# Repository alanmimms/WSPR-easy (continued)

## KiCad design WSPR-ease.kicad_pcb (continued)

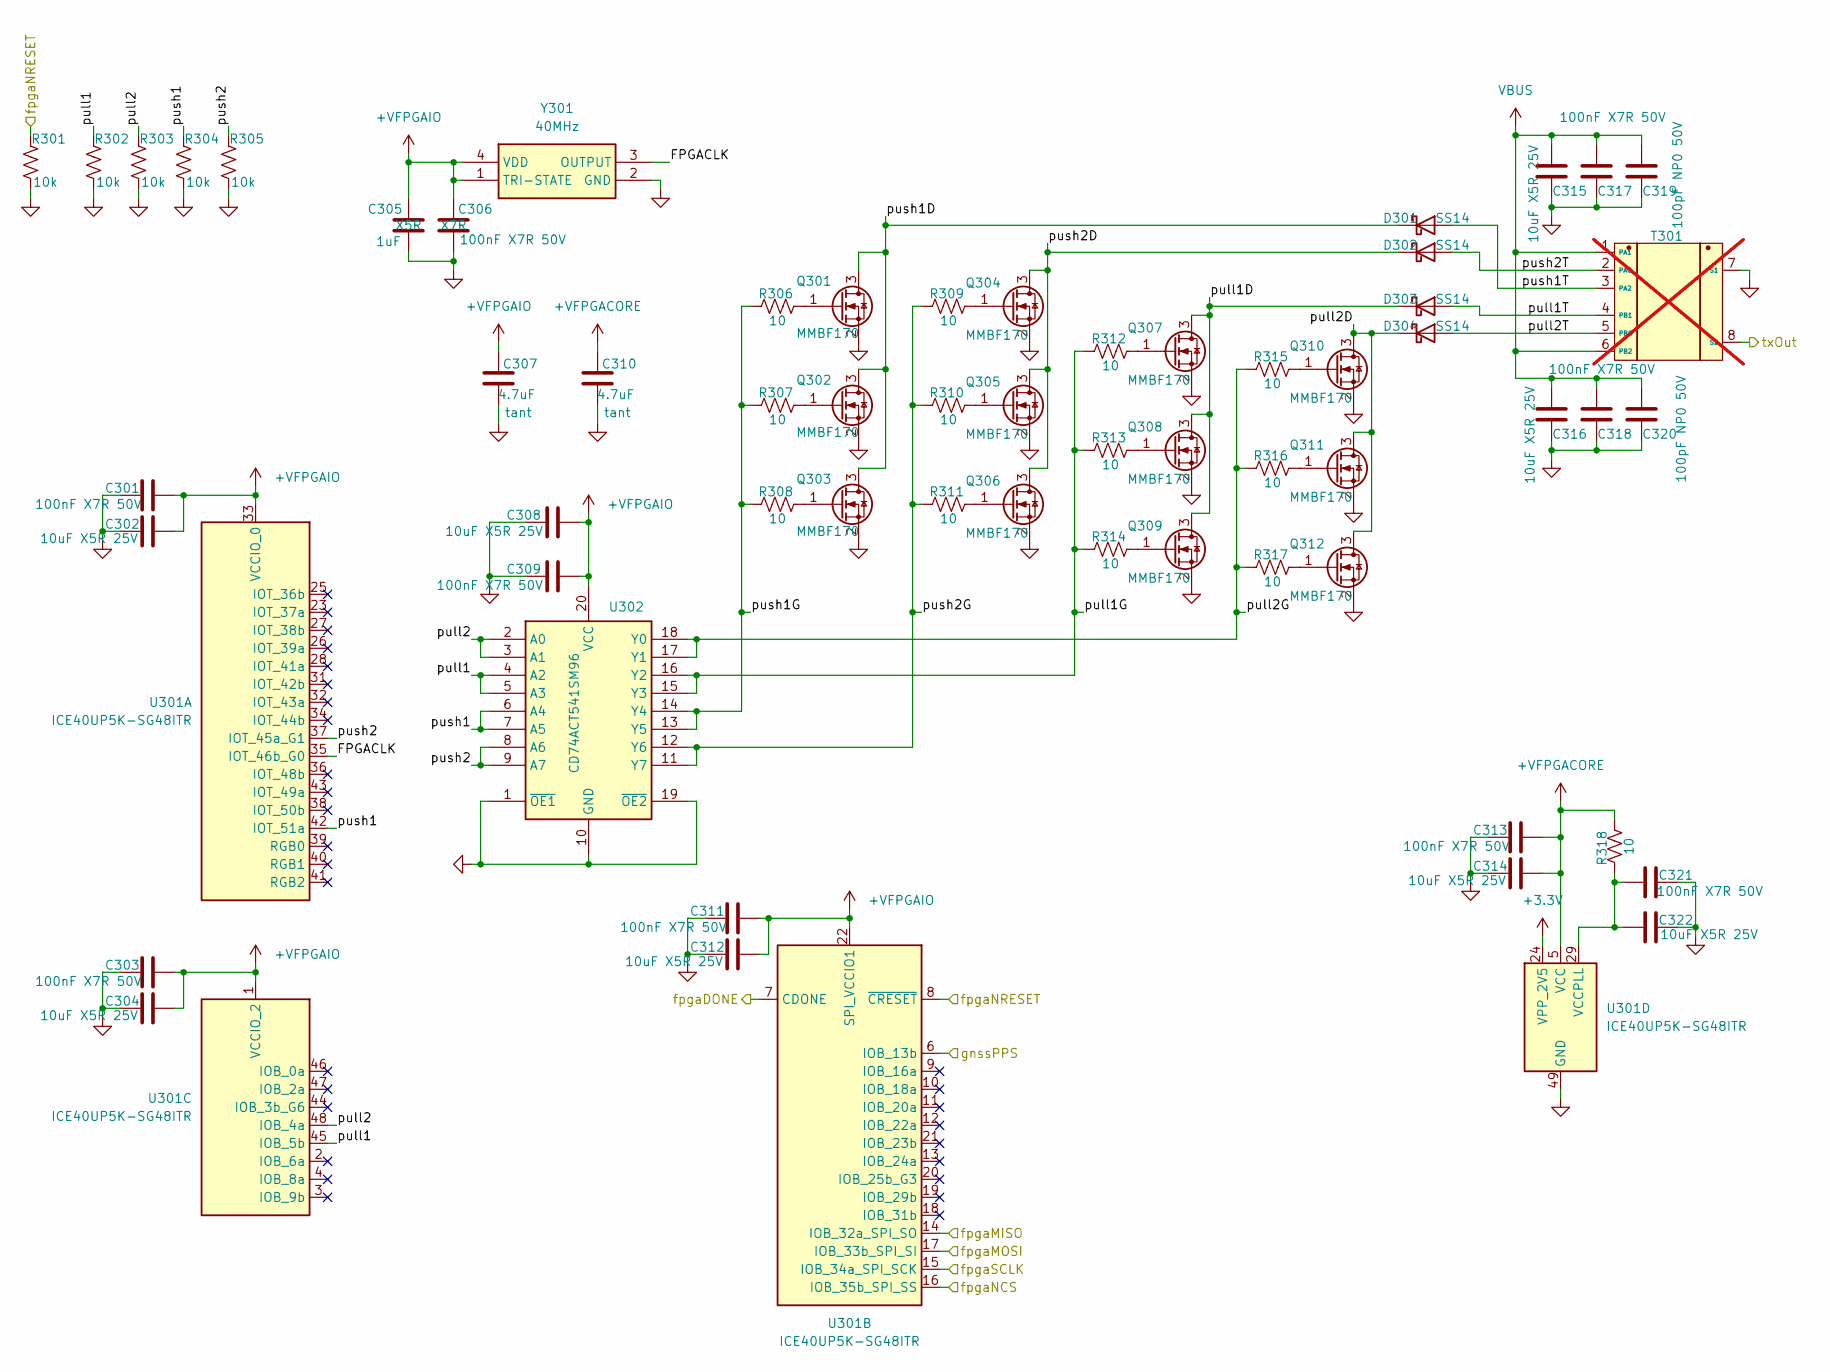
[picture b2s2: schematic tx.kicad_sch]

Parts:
C301, C303, C309, C311, C313, C317, C318, C321: 100nF X7R 50V; C_0603_1608Metric; LCSC C24452
C302, C304, C308, C312, C314, C315, C316, C322: 10uF X5R 25V; C_0603_1608Metric; LCSC C96446
C305: 1uF; C_0402_1005Metric; Mouser_PN 81-GRM155R61E105KE1D; LCSC_PN C301928
C306: 100nF X7R 50V; C_0603_1608Metric; Mouser_PN 80-C0805F104K1RAUTO; LCSC_PN C24452
C307, C310: 4.7uF; C_0402_1005Metric; Mouser_PN 74-298D475X9010M2T; LCSC_PN C18535241
C319, C320: 100pF NP0 50V; C_0402_1005Metric; LCSC C106200
D301, D302, D303, D304: SS14; D_SMA; LCSC C83852
Q301, Q302, Q303, Q304, Q305, Q306, Q307, Q308, Q309, Q310, Q311, Q312: MMBF170; SOT-23; LCSC C28871
R301, R302, R303, R304, R305: 10k; R_0402_1005Metric; LCSC C60490
R306, R307, R308, R309, R310, R311, R312, R313, R314, R315, R316, R317, R318: 10; R_0603_1608Metric; LCSC C2907091
T301: BN-43-202_DualPri_CTSec; bn-43-202-horizontal; MPN 2843000202; LCSC C7174817; not fitted
U301: ICE40UP5K-SG48ITR; QFN-48-1EP_7x7mm_P0.5mm_EP5.6x5.6mm; LCSC C2678152
U302: CD74ACT541SM96; SOP65P780X200-20N; LCSC C553178
Y301: 40MHz; ECSTXO201633400TR; MPN ECS-TXO-2016-33-400-TR; LCSC_PN C2451471

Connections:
+3.3V: U301.24 (VPP_2V5); also elsewhere on the board
+VFPGACORE: C310.1, C313.2, C314.2, R318.2, U301.5 (VCC), U301.30 (VCC); also elsewhere on the board
+VFPGAIO: C301.2, C302.2, C303.2, C304.2, C305.1, C306.1, C307.1, C308.2, C309.2, C311.2, C312.2, U301.1 (VCCIO_2), U301.22 (SPI_VCCIO1), U301.33 (VCCIO_0), U302.20 (VCC), Y301.1 (TRI-STATE), Y301.4 (VDD); also elsewhere on the board
/Low Pass Filters/RFin: T301.8 (S2); also elsewhere on the board
/Transmitter/FPGACLK: U301.35 (IOT_46b_G0), Y301.3 (OUTPUT)
/Transmitter/pull1: R302.1, U301.45 (IOB_5b), U302.4 (A2), U302.5 (A3)
/Transmitter/pull1D: D303.1 (K), Q307.3 (D), Q308.3 (D), Q309.3 (D)
/Transmitter/pull1G: R312.1, R313.1, R314.1, U302.15 (Y3), U302.16 (Y2)
/Transmitter/pull1T: D303.2 (A), T301.4 (PB1)
/Transmitter/pull2: R303.1, U301.48 (IOB_4a), U302.2 (A0), U302.3 (A1)
/Transmitter/pull2D: D304.1 (K), Q310.3 (D), Q311.3 (D), Q312.3 (D)
/Transmitter/pull2G: R315.1, R316.1, R317.1, U302.17 (Y1), U302.18 (Y0)
/Transmitter/pull2T: D304.2 (A), T301.5 (PBC)
/Transmitter/push1: R304.1, U301.42 (IOT_51a), U302.6 (A4), U302.7 (A5)
/Transmitter/push1D: D301.1 (K), Q301.3 (D), Q302.3 (D), Q303.3 (D)
/Transmitter/push1G: R306.1, R307.1, R308.1, U302.13 (Y5), U302.14 (Y4)
/Transmitter/push1T: D301.2 (A), T301.3 (PA2)
/Transmitter/push2: R305.1, U301.37 (IOT_45a_G1), U302.8 (A6), U302.9 (A7)
/Transmitter/push2D: D302.1 (K), Q304.3 (D), Q305.3 (D), Q306.3 (D)
/Transmitter/push2G: R309.1, R310.1, R311.1, U302.11 (Y7), U302.12 (Y6)
/Transmitter/push2T: D302.2 (A), T301.2 (PAC)
/fpgaDONE: U301.7 (CDONE); also elsewhere on the board
/fpgaMISO: U301.14 (IOB_32a_SPI_SO); also elsewhere on the board
/fpgaMOSI: U301.17 (IOB_33b_SPI_SI); also elsewhere on the board
/fpgaNCS: U301.16 (IOB_35b_SPI_SS); also elsewhere on the board
/fpgaNRESET: R301.1, U301.8 (~CRESET); also elsewhere on the board
/fpgaSCLK: U301.15 (IOB_34a_SPI_SCK); also elsewhere on the board
/gnssPPS: U301.6 (IOB_13b); also elsewhere on the board
GND: C301.1, C302.1, C303.1, C304.1, C305.2, C306.2, C307.2, C308.1, C309.1, C310.2, C311.1, C312.1, C313.1, C314.1, C315.1, C316.1, C317.1, C318.1, C319.1, C320.1, C321.1, C322.1, Q301.2 (S), Q302.2 (S), Q303.2 (S), Q304.2 (S), Q305.2 (S), Q306.2 (S), Q307.2 (S), Q308.2 (S), Q309.2 (S), Q310.2 (S), Q311.2 (S), Q312.2 (S), R301.2, R302.2, R303.2, R304.2, R305.2, T301.7 (S1), U301.49 (GND), U302.1 (~OE1), U302.10 (GND), U302.19 (~OE2), Y301.2 (GND); also elsewhere on the board
unnamed: Q301.1 (G), R306.2
unnamed: Q302.1 (G), R307.2
unnamed: Q303.1 (G), R308.2
unnamed: Q304.1 (G), R309.2
unnamed: Q305.1 (G), R310.2
unnamed: Q306.1 (G), R311.2
unnamed: Q307.1 (G), R312.2
unnamed: Q308.1 (G), R313.2
unnamed: Q309.1 (G), R314.2
unnamed: Q310.1 (G), R315.2
unnamed: Q311.1 (G), R316.2
unnamed: Q312.1 (G), R317.2
unnamed: C321.2, C322.2, R318.1, U301.29 (VCCPLL)
VBUS: C315.2, C316.2, C317.2, C318.2, C319.2, C320.2, T301.1 (PA1), T301.6 (PB2); also elsewhere on the board

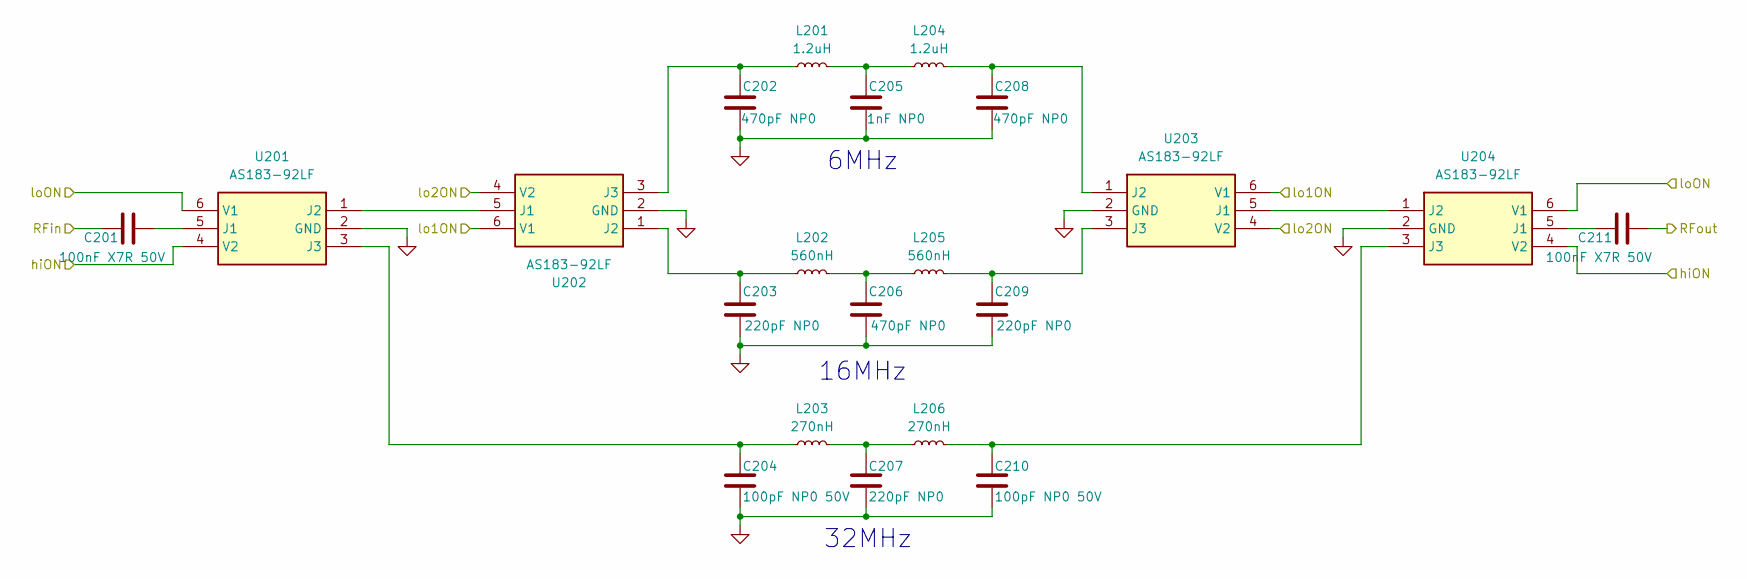
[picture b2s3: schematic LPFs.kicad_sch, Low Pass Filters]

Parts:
C201, C211: 100nF X7R 50V; C_0603_1608Metric; LCSC C24452
C202, C206, C208: 470pF NP0; C_0402_1005Metric; LCSC C106259
C203, C207, C209: 220pF NP0; C_0402_1005Metric; LCSC C107001
C204, C210: 100pF NP0 50V; C_0402_1005Metric; LCSC C106200
C205: 1nF NP0; C_0402_1005Metric; LCSC C5182455
L201, L204: 1.2uH; L_1008_2520Metric; Mouser Part Number 1008LS-222; LCSC C2044063
L202, L205: 560nH; L_0805_2012Metric; Mouser Part Number 0805CS-391XGLC; LCSC C6364717
L203, L206: 270nH; L_0805_2012Metric; Mouser Part Number 0805CS-271 XGLC; LCSC C404430
U201, U202, U203, U204: AS183-92LF; SOT65P220X110-6N; Mouser Part Number 873-AS183-92LF

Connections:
/Low Pass Filters/RFin: C201.1; also elsewhere on the board
/Low Pass Filters/RFout: C211.2; also elsewhere on the board
/hiON: U201.4 (V2), U204.4 (V2); also elsewhere on the board
/lo1ON: U202.6 (V1), U203.6 (V1); also elsewhere on the board
/lo2ON: U202.4 (V2), U203.4 (V2); also elsewhere on the board
/loON: U201.6 (V1), U204.6 (V1); also elsewhere on the board
GND: C202.2, C203.2, C204.2, C205.2, C206.2, C207.2, C208.2, C209.2, C210.2, U201.2 (GND), U202.2 (GND), U203.2 (GND), U204.2 (GND); also elsewhere on the board
unnamed: C205.1, L201.2, L204.1
unnamed: C206.1, L202.2, L205.1
unnamed: C207.1, L203.2, L206.1
unnamed: C201.2, U201.5 (J1)
unnamed: U201.1 (J2), U202.5 (J1)
unnamed: C204.1, L203.1, U201.3 (J3)
unnamed: C203.1, L202.1, U202.1 (J2)
unnamed: C202.1, L201.1, U202.3 (J3)
unnamed: U203.5 (J1), U204.1 (J2)
unnamed: C208.1, L204.2, U203.1 (J2)
unnamed: C209.1, L205.2, U203.3 (J3)
unnamed: C211.1, U204.5 (J1)
unnamed: C210.1, L206.2, U204.3 (J3)

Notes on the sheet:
6MHz
32MHz
16MHz

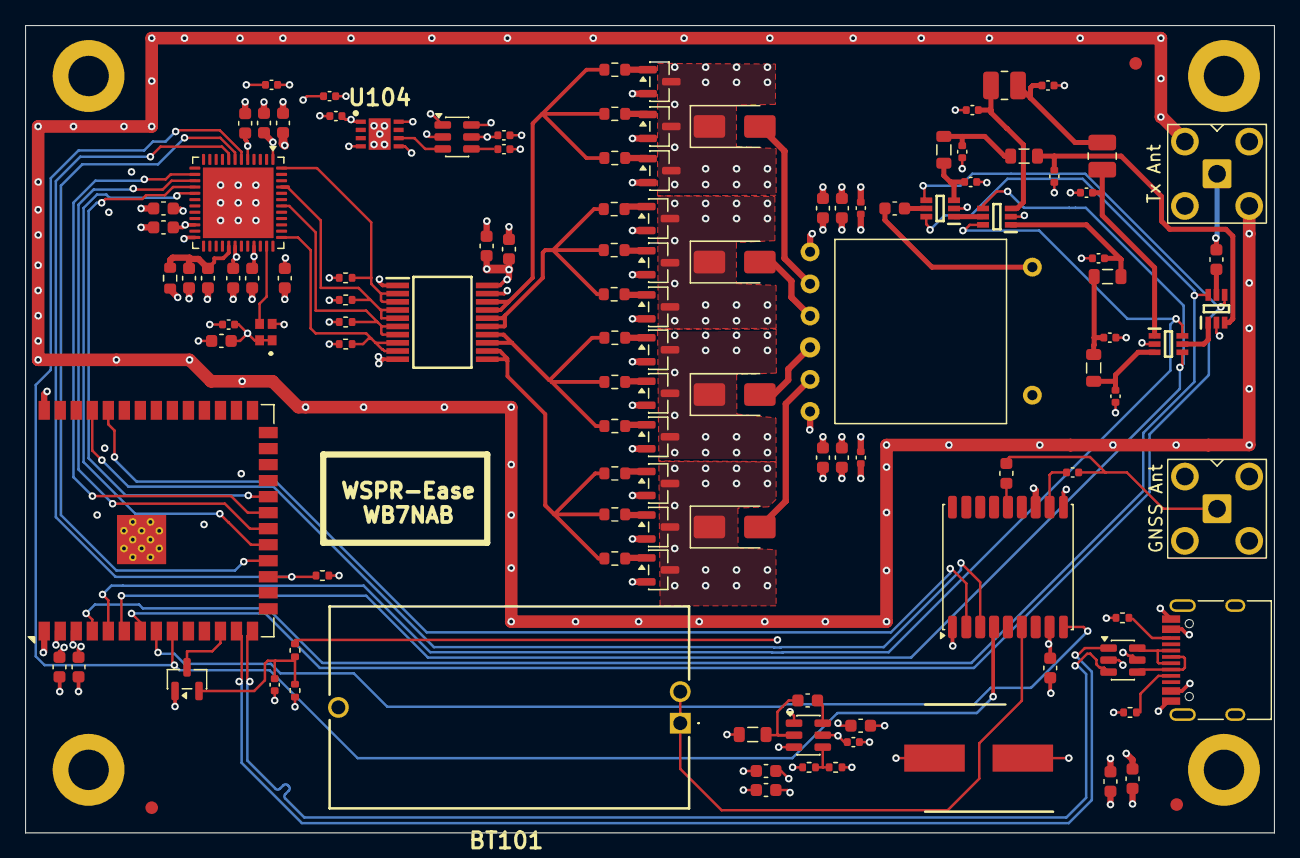
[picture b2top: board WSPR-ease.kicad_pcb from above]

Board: 4 copper layers, 99.0 x 64.0 mm, 123 parts (0 on the bottom side), 81 nets.

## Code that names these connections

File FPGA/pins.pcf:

# Clock Inputs
set_io fpgaSCLK_pin 15
set_io clk40 35
set_io gnssPPS 6

# SPI Interface (Standard 4mA is fine for these)
set_io fpgaMOSI 17
set_io fpgaNCS 16
set_io fpgaMISO 14

# RF Exciter Outputs (DDR Capable, 12mA High Drive)
set_io rfPushBase 42
set_io rfPushPeak 37
set_io rfPullBase 45
set_io rfPullPeak 48
set_io driverNEN 25

# Reset without reconfiguration
set_io fpgaNRESET 36

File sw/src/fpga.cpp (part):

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								   {"spi", "pps", "config", "bitstream"});

  // GPIO specs from devicetree (All configured as GPIO_ACTIVE_HIGH in overlay)
  static const struct gpio_dt_spec fpgaCRESET = GPIO_DT_SPEC_GET(DT_NODELABEL(fpga_creset), gpios);
  static const struct gpio_dt_spec fpgaDONE = GPIO_DT_SPEC_GET(DT_NODELABEL(fpga_done), gpios);
  static const struct gpio_dt_spec fpgaNCS = GPIO_DT_SPEC_GET(DT_NODELABEL(fpga_ncs), gpios);

  static const struct gpio_dt_spec fpgaNRESET = GPIO_DT_SPEC_GET(DT_NODELABEL(fpga_nreset), gpios);

  static const struct gpio_dt_spec pgFPGACORE = GPIO_DT_SPEC_GET(DT_NODELABEL(pg_fpgacore), gpios);
  static const struct gpio_dt_spec enFPGAIO = GPIO_DT_SPEC_GET(DT_NODELABEL(en_fpgaio), gpios);

  // iCE40 Slave SPI: Mode 0 (CPOL=0, CPHA=0), MSB First.
  static const struct spi_dt_spec fpgaSPI = SPI_DT_SPEC_GET(DT_NODELABEL(fpga_dev),
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
    // MANDATE: Explicitly start with enFPGAIO DEASSERTED (Physical Low).
    // The hardware has a 10k pulldown, but we ensure it in software too.
    gpio_pin_configure_dt(&enFPGAIO, GPIO_OUTPUT_LOW);

    // Hold FPGA in config reset and set CS LOW for SPI slave mode
    gpio_pin_configure_dt(&fpgaNRESET, GPIO_OUTPUT_LOW);
    gpio_pin_configure_dt(&fpgaCRESET, GPIO_OUTPUT_LOW);
    gpio_pin_configure_dt(&fpgaNCS, GPIO_OUTPUT_LOW);
    gpio_pin_configure_dt(&pgFPGACORE, GPIO_INPUT);
    gpio_pin_configure_dt(&fpgaDONE, GPIO_INPUT | GPIO_PULL_UP);

    logger.inf("enFPGAIO deasserted. Waiting for FPGA Core power good (pgFPGACORE)...");

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
    while (!pgOK && k_uptime_get_32() - startTime < 1000) {

      if (gpio_pin_get_dt(&pgFPGACORE) > 0) {
	pgOK = true;
	logger.inf("pgFPGACORE asserted after %u ms", k_uptime_get_32() - startTime);
      }
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
    // Enable FPGA IO Power
    logger.inf("Enabling FPGA IO power (enFPGAIO)...");
    gpio_pin_set_dt(&enFPGAIO, 1); // Physical High
    k_msleep(100); // Stabilization delay

    // Proceed with configuration
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  }

  int FPGA::reset() {
    gpio_pin_set_dt(&fpgaNRESET, 0);	// Assert software reset
    gpio_pin_set_dt(&fpgaNCS, 0);	// SPI slave mode indicator
    gpio_pin_set_dt(&fpgaCRESET, 0);	// Assert FPGA config reset
    k_msleep(1);
    gpio_pin_set_dt(&fpgaCRESET, 1);	// Release FPGA config reset
    k_msleep(2);
    gpio_pin_set_dt(&fpgaNCS, 1);	// Return SPI NCS to deasserted idle state

    if (gpio_pin_get_dt(&fpgaDONE) > 0) {
      logger.err("FPGA Error: CDONE is HIGH immediately after reset pulse!");
      return -EIO;
    }

    // Release software reset when chip is fully operational.
    k_msleep(1);
    gpio_pin_set_dt(&fpgaNRESET, 1);
    return 0;
  }

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      return -EIO;
    }

    gpio_pin_set_dt(&fpgaNCS, 0);
    uint8_t dummy = 0x00;
    struct spi_buf sDummy = { .buf = &dummy, .len = 1 };
    struct spi_buf_set sDummies = { .buffers = &sDummy, .count = 1 };
    spi_write_dt(&fpgaSPI, &sDummies);
    gpio_pin_set_dt(&fpgaNCS, 1);

    logger.inf("bitstream", "Transmitting bitstream...");

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	logger.err("bitstream", "SPI write error at %zu: %d", totalBytes, ret);
	k_free(buffer);
	fs_close(&file);
	gpio_pin_set_dt(&fpgaNCS, 1);
	return ret;
      }
      totalBytes += bytesRead;
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    fs_close(&file);
    logger.inf("bitstream", "Transmitted %zu bytes", totalBytes);

    gpio_pin_set_dt(&fpgaNCS, 1);

    bool success = false;
    for (int i = 0; i < 100; i++) {

      if (gpio_pin_get_dt(&fpgaDONE) > 0) {
	success = true;
	break;
      }
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    txBuf[3] = (value >> 8) & 0xFF;
    txBuf[4] = value & 0xFF;

    gpio_pin_set_dt(&fpgaNCS, 0);
    struct spi_buf sBuf = { .buf = txBuf, .len = sizeof(txBuf) };
    struct spi_buf_set sBufs = { .buffers = &sBuf, .count = 1 };
    int ret = spi_write_dt(&fpgaSPI, &sBufs);
    gpio_pin_set_dt(&fpgaNCS, 1);
    return ret;
  }

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    uint8_t txBuf[5] = { (uint8_t)(reg & 0x7F), 0, 0, 0, 0 };
    uint8_t rxBuf[5] = { 0 };

    gpio_pin_set_dt(&fpgaNCS, 0);
    struct spi_buf sTX = { .buf = txBuf, .len = 5 };
    struct spi_buf_set sTXs = { .buffers = &sTX, .count = 1 };
    struct spi_buf sRX = { .buf = rxBuf, .len = 5 };
    struct spi_buf_set sRXs = { .buffers = &sRX, .count = 1 };
    int ret = spi_transceive_dt(&fpgaSPI, &sTXs, &sRXs);
    gpio_pin_set_dt(&fpgaNCS, 1);

    if (ret == 0) {
      // Data is in rxBuf[1..4] because Byte 0 was the address/command
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
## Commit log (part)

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2025-11-25 initial
2025-11-26 Starting layout a bit
2025-11-26 Documentation
2025-11-27 Fix filters for proper response. Now we have FPGA + ESP32S3.
2025-11-29 Well it is routed and passes DRC
2025-11-29 Minor tweaks after submitting 001 build to pcbway
2025-12-02 Submitted to PCBway (I had to update BOM after oops)
2025-12-03 Cleanup. Better USB diff pair with 0ohm and TVS as recommended. Return to rectangular outline and even smaller. Mounting holes are consistently placed relative to board corners.
2025-12-04 Ignore some binaries and logs
2025-12-06 Starting to run on ESP32S3 dev board for now until hw arrives
2025-12-06 Fix some naming
2025-12-06 Add script, ignore build dir.
2025-12-07 Add stitching vias to ground ring around RF zone
2025-12-07 Switch to SSOP package for 74ACT541. Tweak a bunch of layout for DFM and maybe some improved SI.
2025-12-07 Fix up 3d in footprints in lib so they stay put when I update PCB from schematic. Fix text labels for same issue.
2025-12-15 Some PCBWay clarifications
2025-12-15 checkpoint
2026-01-05 Fixes to pass ERC. Nothing serious really.
2026-03-02 Tarted up, 3d models applied, better footprints and BOM, ready to submit for PCBA
2026-03-02 Small changes to part numbers to ease supply chain issues for build
2026-03-03 Clean up signal quality and noise incursion into GNSS by moving some traces around
2026-03-03 This filename has always bugged me
2026-03-03 Reorg some dirs for tidiness
2026-03-03 Fix up 3d paths
2026-03-15 Clean up some clearances found by FlashPCB tools
2026-03-18 Cleanup and prep for MacroFab quote
2026-03-25 Parts ordered for DVT1 build
2026-03-26 About to redo the layout of the tx gate controls to match lengths
2026-03-28 Fix huge oopsie with USB diode protection after having fixed the unforgivable polarity reversal and NOT SEEING THIS BUG. I can be an idiot sometimes.
2026-03-29 Testing on real hardware! And other than a D+/D- swap on USB it seems to work so far.
2026-03-29 Seems like it saves callsign and grid square properly now
2026-03-29 Now saving and actually restoring config from flash
2026-03-29 Oops. Rx and Tx need to be swapped on GNSS
2026-03-29 Flash on nano1 remote host with WSPR-ease board attached to its USB
2026-03-29 Fixed reversed rx/tx on GNSS chip. Solved all ERC and DRC issues
2026-03-30 Implement real GNSS hardware integration with reset pulse and UART0 migration
2026-03-30 Functional but without FPGA loading working well yet
2026-03-31 Still working on FPGA config loading. Problem is now CMOS lockup caused by FPGACORE vs FPGAIO rails. I moved FPGAIO enable to IO42 on ESP32 and pgFPGACORE to IO41.
2026-03-31 Rename-o-rama to make coding style match my explicit guidelines (GEMINI ignores these for some reason). I have cleaned a few things up in the process. Code is somewhat broken right now as I prep for 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
2026-04-01 Refactor LittleFS to singleton, optimize memory usage, and fix FPGA power sequencing
    - Refactored LittleFS management into a wspr::FileSystem singleton
    - Moved thread stacks (WebServer, GNSS) and request buffers to the heap to reduce BSS usage and avoid DRAM overflow
    - Optimized FPGA bitstream loading with proper power sequencing for core and IO rails
    - Updated app.overlay with a clean partition table (explicitly deleting default partitions)
    - Updated flash-lfs.sh to extract partition info directly from zephyr.dts (single source of truth)
    - Improved WebServer stability and error logging for NVS configuration
2026-04-01 Update docs to current fact
2026-04-01 Add 10k pullup to +3.3V for PG on FPGA CORE rail so we can read it from ESP32.
2026-04-02 Fix FPGA RF output and status reporting
    - Fixed FPGA SB_IO drive by connecting the clock and output enable
    - Corrected status bit alignment and added a heartbeat bit to FPGA registers
    - Improved FPGA build system and simulation test cases
    - Added initial LogManager and enhanced ESP32 shell commands for FPGA diagnostics
2026-04-02 Start on the path to doing logging right, but still not great. Clean up some graphics in schematics
2026-04-02 Get rid of Claude history
2026-04-02 Move this into hw where it belongs
2026-04-02 Build at top level now. Add two snapshot registers to FPGA 40MHz counter to get true 1pps delta. Add some more built in and new wspr shell commands for debugging and curiousity.
2026-04-03 Now committed to using ESP32 sw to control modulation in realtime (1.6Hz is really easy). FPGA is timing now, but there is jitter on the output at 5.555555MHz. About to try another approach doing sep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
2026-04-06 Separate FPGA config CRESET from software NRESET, add RGB heartbeat to FPGA.
2026-04-09 FPGA loading again. 5.555555MHz tx is jittery again.
2026-04-10 FPGA: Update PLL to 90MHz for 180MHz DDR RF output and optimize NCO pipeline for timing.
    - Updated PLL in top.sv to output 90MHz from 40MHz input.
    - Refactored WSPRExciter.sv with 8-stage 4-bit pipelined NCO to hit 90MHz timing.
    - Added explicit SB_GB buffers for clk90 and fpgaSCLK.
    - Updated simulation (tbTop.cpp, simHAL.hpp) and view_waveform.py.
    - Adjusted doc/SYSTEM_NOTES.md and sw/src/fpga.cpp constants to match 90MHz (180Msps DDR).
2026-04-10 FPGA: Fix NCO jitter via bit deskewing, optimize DDR timing, and correct frequency scaling.
    - Implemented bit deskewing in WSPRExciter.sv to align 4-bit NCO stages into a coherent 16-bit phase, resolving jitter.
    - Moved falling-edge DDR outputs to negedge registers to eliminate 5.5ns half-cycle bottlenecks.
    - Corrected sw/src/fpga.cpp to use 90MHz for tuning word calculation (fixed 2.25x scaling error).
    - Added synchronized reset for 90MHz domain in top.sv.
    - Added timescale declarations to all .sv files to fix Verilator warnings.
2026-04-10 Move to single gate buffer per MOSFET to distribute decoupling and gate drive across more devices and improve gate drive signal quality at high speed
2026-04-10 These pins actually match the schematic
2026-04-10 Not used
2026-04-10 Ignore build dir and delete unused script
2026-04-11 Refactor shell commands: remove wspr prefix and redesign tx command
2026-04-11 Normalize line endings to LF via .gitattributes
2026-04-11 Make my "/initbrain" skill actually get the info into context that I need for project
2026-04-11 Fix CRLF newlines
2026-04-11 Another try. Timing closes. No FPGA output for 1 or 5MHz. Checkpoint.
2026-04-11 Make sure we send power 255 in control SPI write
2026-04-11 Add reboot command. Log when FPGA PLL is not locked but it has been loaded.
2026-04-11 Make it actually compile
